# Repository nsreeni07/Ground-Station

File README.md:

# Ground-Station
My own Custom Lora Ground Station for Amateur Rocketry

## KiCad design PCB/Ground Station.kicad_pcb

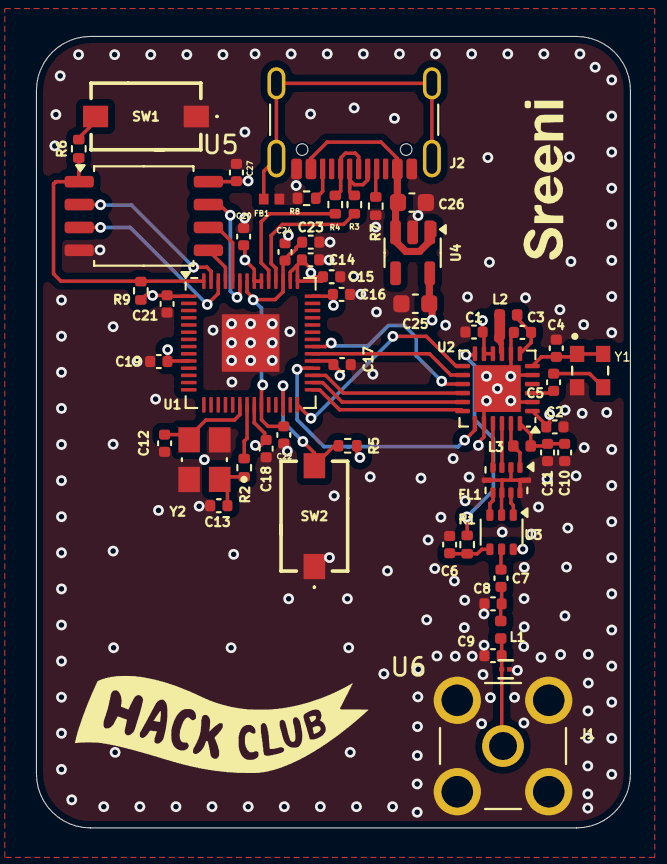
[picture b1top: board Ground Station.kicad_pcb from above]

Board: 4 copper layers, 33.0 x 44.0 mm, 53 parts (0 on the bottom side), 45 nets.

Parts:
C1, C2, C4, C14, C15, C16, C17, C18, C19, C20, C22, C23, C27: 100 nF; C_0402_1005Metric
C3: 470 nF; C_0402_1005Metric
C5: 100 pF; C_0402_1005Metric
C6: 1 nF; C_0402_1005Metric
C7: 39 pF; C_0402_1005Metric
C8, C9: 3.3 pF; C_0402_1005Metric
C10, C11: 47 nF; C_0402_1005Metric
C12, C13: 27 pF; C_0402_1005Metric
C21, C24: 1 uF; C_0402_1005Metric
C25, C26: 10 uF; C_0603_1608Metric
FB1: BLM15AX102SN1D; BEADC1005X55N
FL1: 0900FM15K0039; Balun_Johanson_0900FM15K0039
J1: RFPC-SMA28-F; GRADCONN_RFPC-SMA28-F
J2: USB_C_Receptacle_USB2.0_14P; USB_C_Receptacle_GCT_USB4105-xx-A_16P_TopMnt_Horizontal
L1: 15 nH; L_0402_1005Metric
L2: 15 uH; L_0402_1005Metric
L3: 47 nH; L_0402_1005Metric
R1: 100; R_0402_1005Metric
R2: 1K; R_0402_1005Metric
R3, R4: 27.3; R_0402_1005Metric
R5, R9: 10k; R_0402_1005Metric
R6: 1k; R_0402_1005Metric
R7, R8: 5.1k; R_0402_1005Metric
SW1: BOOT; PTS636SMG25JSMTRLFS
SW2: RESET; PTS636SMG25JSMTRLFS
U1: RP2040; QFN-56-1EP_7x7mm_P0.4mm_EP3.2x3.2mm
U2: SX1262IMLTRT; QFN-24-1EP_4x4mm_P0.5mm_EP2.6x2.6mm
U3: PE4259; SOT-363_SC-70-6
U4: AP2112K-3.3; SOT-23-5
U5: W25Q128JVS; SOIC-8_5.3x5.3mm_P1.27mm
U6: TPD1E0B04DPLR; DPL0002A-MFG
Y1: ECS-TXO-25CSMV-320-DY-TR; OSC_ECS-TXO-25CSMV-320-DY-TR
Y2: ABM8G-12.000MHZ-18-D2Y-T; XTAL_ABM8G-12.000MHZ-18-D2Y-T

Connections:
+1.1: C22.1, C23.1, C24.2, U1.23 (DVDD), U1.45 (VREG_VOUT), U1.50 (DVDD)
+3.3V: C1.1, C2.2, C14.1, C15.1, C16.1, C17.1, C18.1, C19.1, C20.1, C21.1, C25.2, C27.2, R5.2, R9.1, U1.1 (IOVDD), U1.10 (IOVDD), U1.22 (IOVDD), U1.33 (IOVDD), U1.42 (IOVDD), U1.43 (ADC_AVDD), U1.44 (VREG_IN), U1.48 (USB_VDD), U1.49 (IOVDD), U2.1 (VDD_IN), U2.10 (VBAT), U2.11 (VBAT_IO), U3.6 (VDD), U4.5 (VOUT), U5.8 (VCC)
/BUSY: U1.34 (GPIO22), U2.14 (BUSY)
/DIO1: U1.28 (GPIO17), U2.13 (DIO1)
/DIO2: R1.1, U2.12 (DIO2)
/DIO3: C4.2, U2.6 (DIO3), Y1.1 (TRI_STATE), Y1.4 (VDD)
/MISO: U1.31 (GPIO20), U2.16 (MISO)
/MOSI: U1.30 (GPIO19), U2.17 (MOSI)
/NSS: U1.32 (GPIO21), U2.19 (NSS)
/QSPI_SCLK: U1.52 (QSPI_SCLK), U5.6 (CLK)
/QSPI_SD0: U1.53 (QSPI_SD0), U5.5 (DI/IO_{0})
/QSPI_SD1: U1.55 (QSPI_SD1), U5.2 (DO/IO_{1})
/QSPI_SD2: U1.54 (QSPI_SD2), U5.3 (~WP/IO_{2})
/QSPI_SD3: U1.51 (QSPI_SD3), U5.7 (~HOLD/~RESET/IO_{3})
/QSPI_SS: R6.2, R9.2, U1.56 (QSPI_SS), U5.1 (~CS)
/RFI_N: FL1.3 (RFI_N), U2.22 (RFI_N)
/RFI_P: FL1.4 (RFI_P), U2.21 (RFI_P)
/RFO: FL1.1 (RFO), L3.2, U2.23 (RFO)
/RST: U1.35 (GPIO23), U2.15 (~RESET)
/RUN: R5.1, SW2.2, U1.26 (RUN)
/SCK: U1.29 (GPIO18), U2.18 (SCK)
/USB_D_N: J2.A7 (D-), J2.B7 (D-), R3.2
/USB_D_P: J2.A6 (D+), J2.B6 (D+), R4.1
/VR_PA: C10.2, C11.2, L3.1, U2.24 (VR_PA)
/XIN: C12.2, U1.20 (XIN), Y2.3
/XOUT: R2.2, U1.21 (XOUT)
/XTA: C5.1, U2.3 (XTA)
Earth: C1.2, C2.1, C3.2, C4.1, C6.1, C8.1, C9.1, C10.1, C11.1, C12.1, C13.2, C14.2, C15.2, C16.2, C17.2, C18.2, C19.2, C20.2, C21.2, C22.2, C23.2, C24.1, C25.1, C26.1, C27.1, FB1.2, FL1.2 (GND), FL1.5 (GND), FL1.7 (GND), FL1.9 (GND), FL1.10 (GND), J1.G1, J1.G2, J1.G3, J1.G4, J2.A1 (GND), J2.A12 (GND), J2.B1 (GND), J2.B12 (GND), R7.2, R8.2, SW1.1, SW2.1, U1.57 (GND), U2.2 (GND), U2.5 (GND), U2.8 (GND), U2.20 (GND), U2.25 (GND), U3.2 (GND), U4.2 (GND), U5.4 (GND), U6.2 (2_IO), Y1.2 (GND), Y2.2 (GND), Y2.4 (GND__1)
unnamed: C7.2, C8.2, L1.1
unnamed: C13.1, R2.1, Y2.1
unnamed: FL1.6 (SW_RFI), U3.3 (RF2)
unnamed: FL1.8 (SW_RFO), U3.1 (RF1)
unnamed: J2.A5 (CC1), R7.1
unnamed: J2.B5 (CC2), R8.1
unnamed: FB1.1, J2.S1 (SHIELD)
unnamed: R6.1, SW1.2
unnamed: R3.1, U1.46 (USB_DM)
unnamed: R4.2, U1.47 (USB_DP)
unnamed: L2.2, U2.9 (DCC_SW)
unnamed: C3.1, L2.1, U2.7 (VREG)
unnamed: C6.2, R1.2, U3.4 (CTRL)
unnamed: C7.1, U3.5 (RFIN)
unnamed: C9.2, J1.1, L1.2, U6.1 (1_IO)
unnamed: C5.2, Y1.3 (OUTPUT)
VBUS: C26.2, J2.A4 (VBUS), J2.A9 (VBUS), J2.B4 (VBUS), J2.B9 (VBUS), U4.1 (VIN), U4.3 (EN)
